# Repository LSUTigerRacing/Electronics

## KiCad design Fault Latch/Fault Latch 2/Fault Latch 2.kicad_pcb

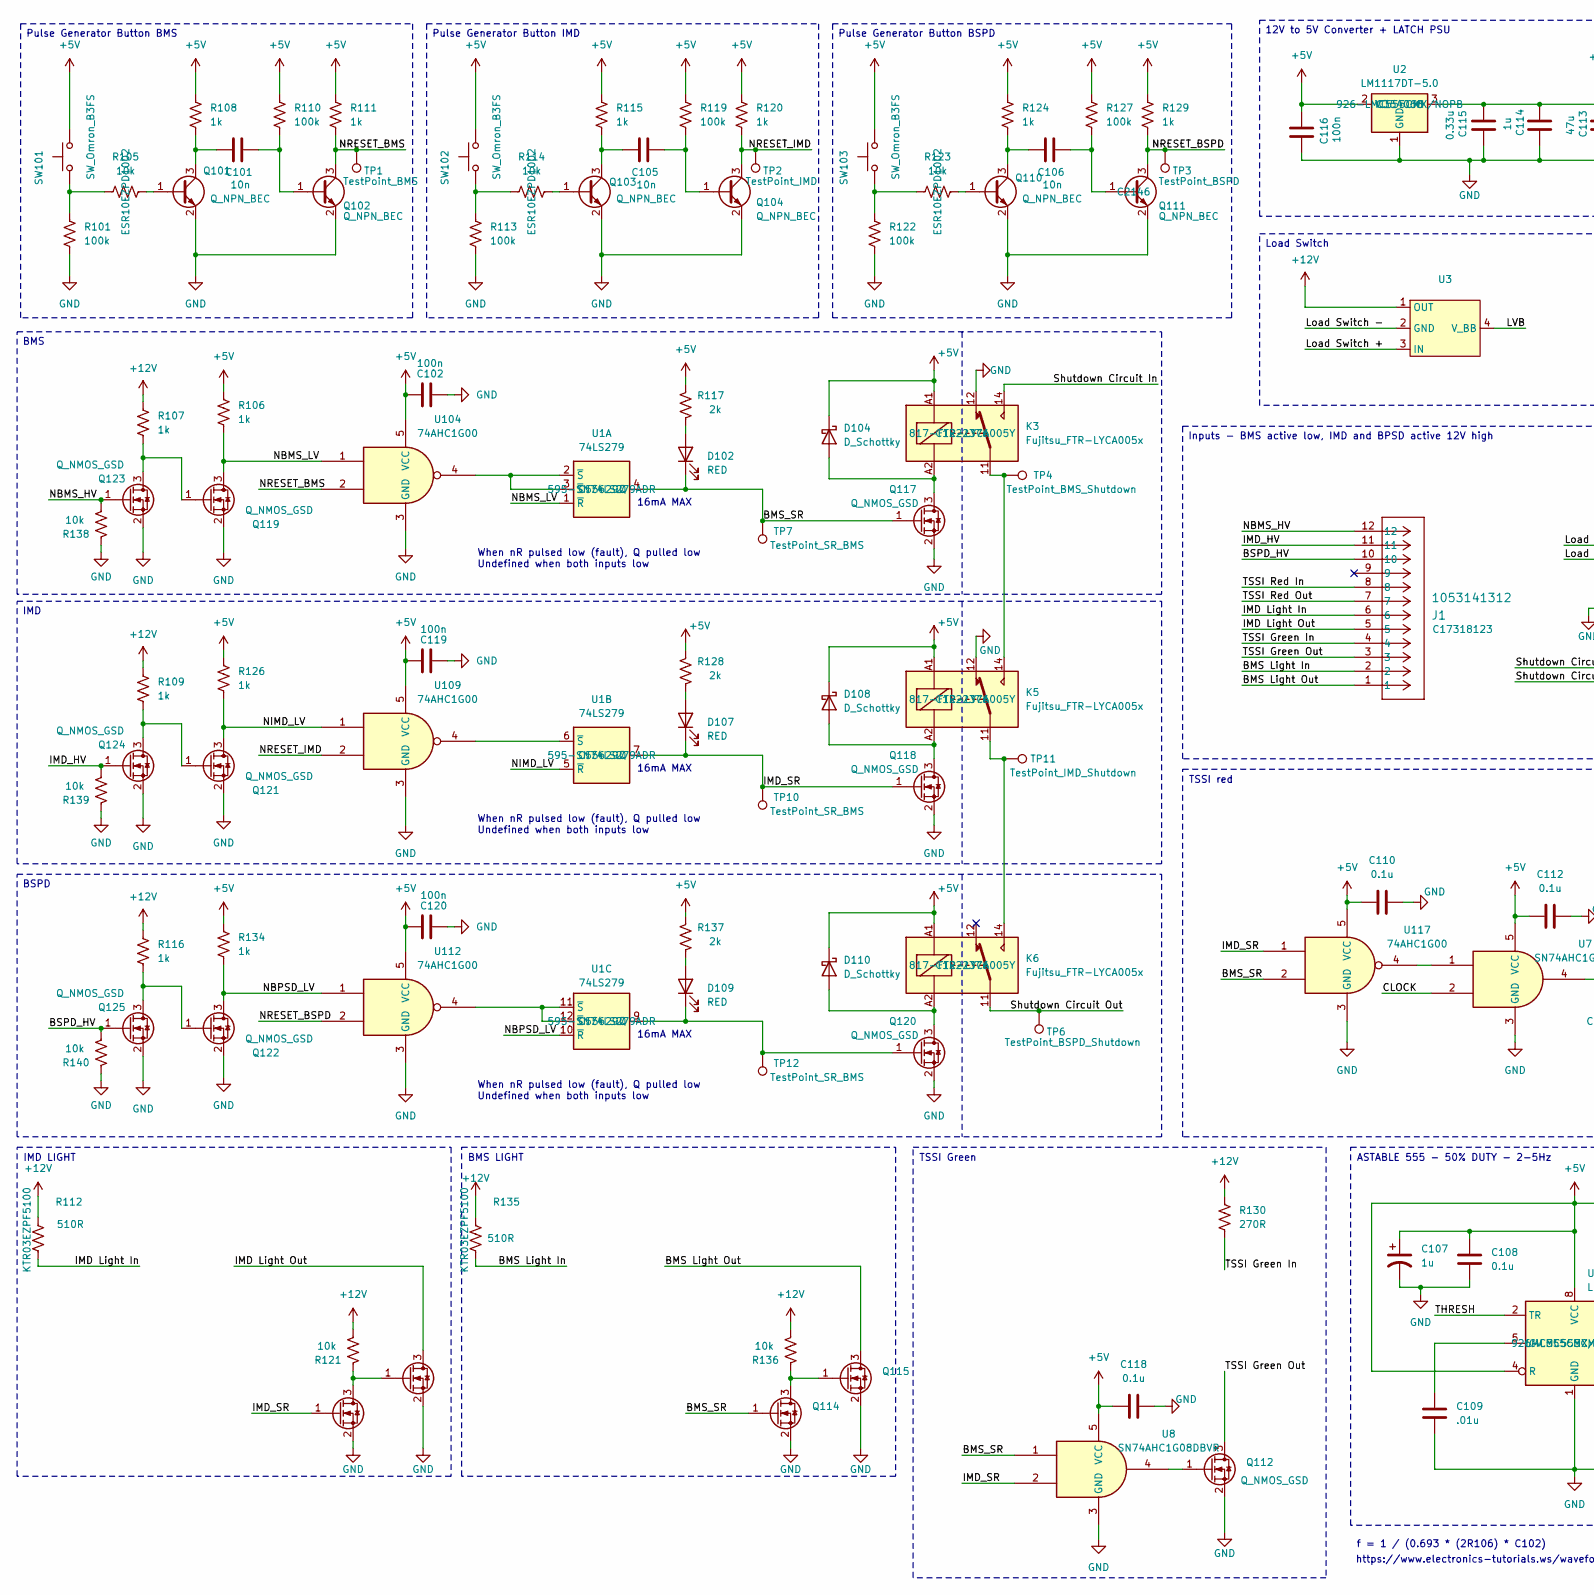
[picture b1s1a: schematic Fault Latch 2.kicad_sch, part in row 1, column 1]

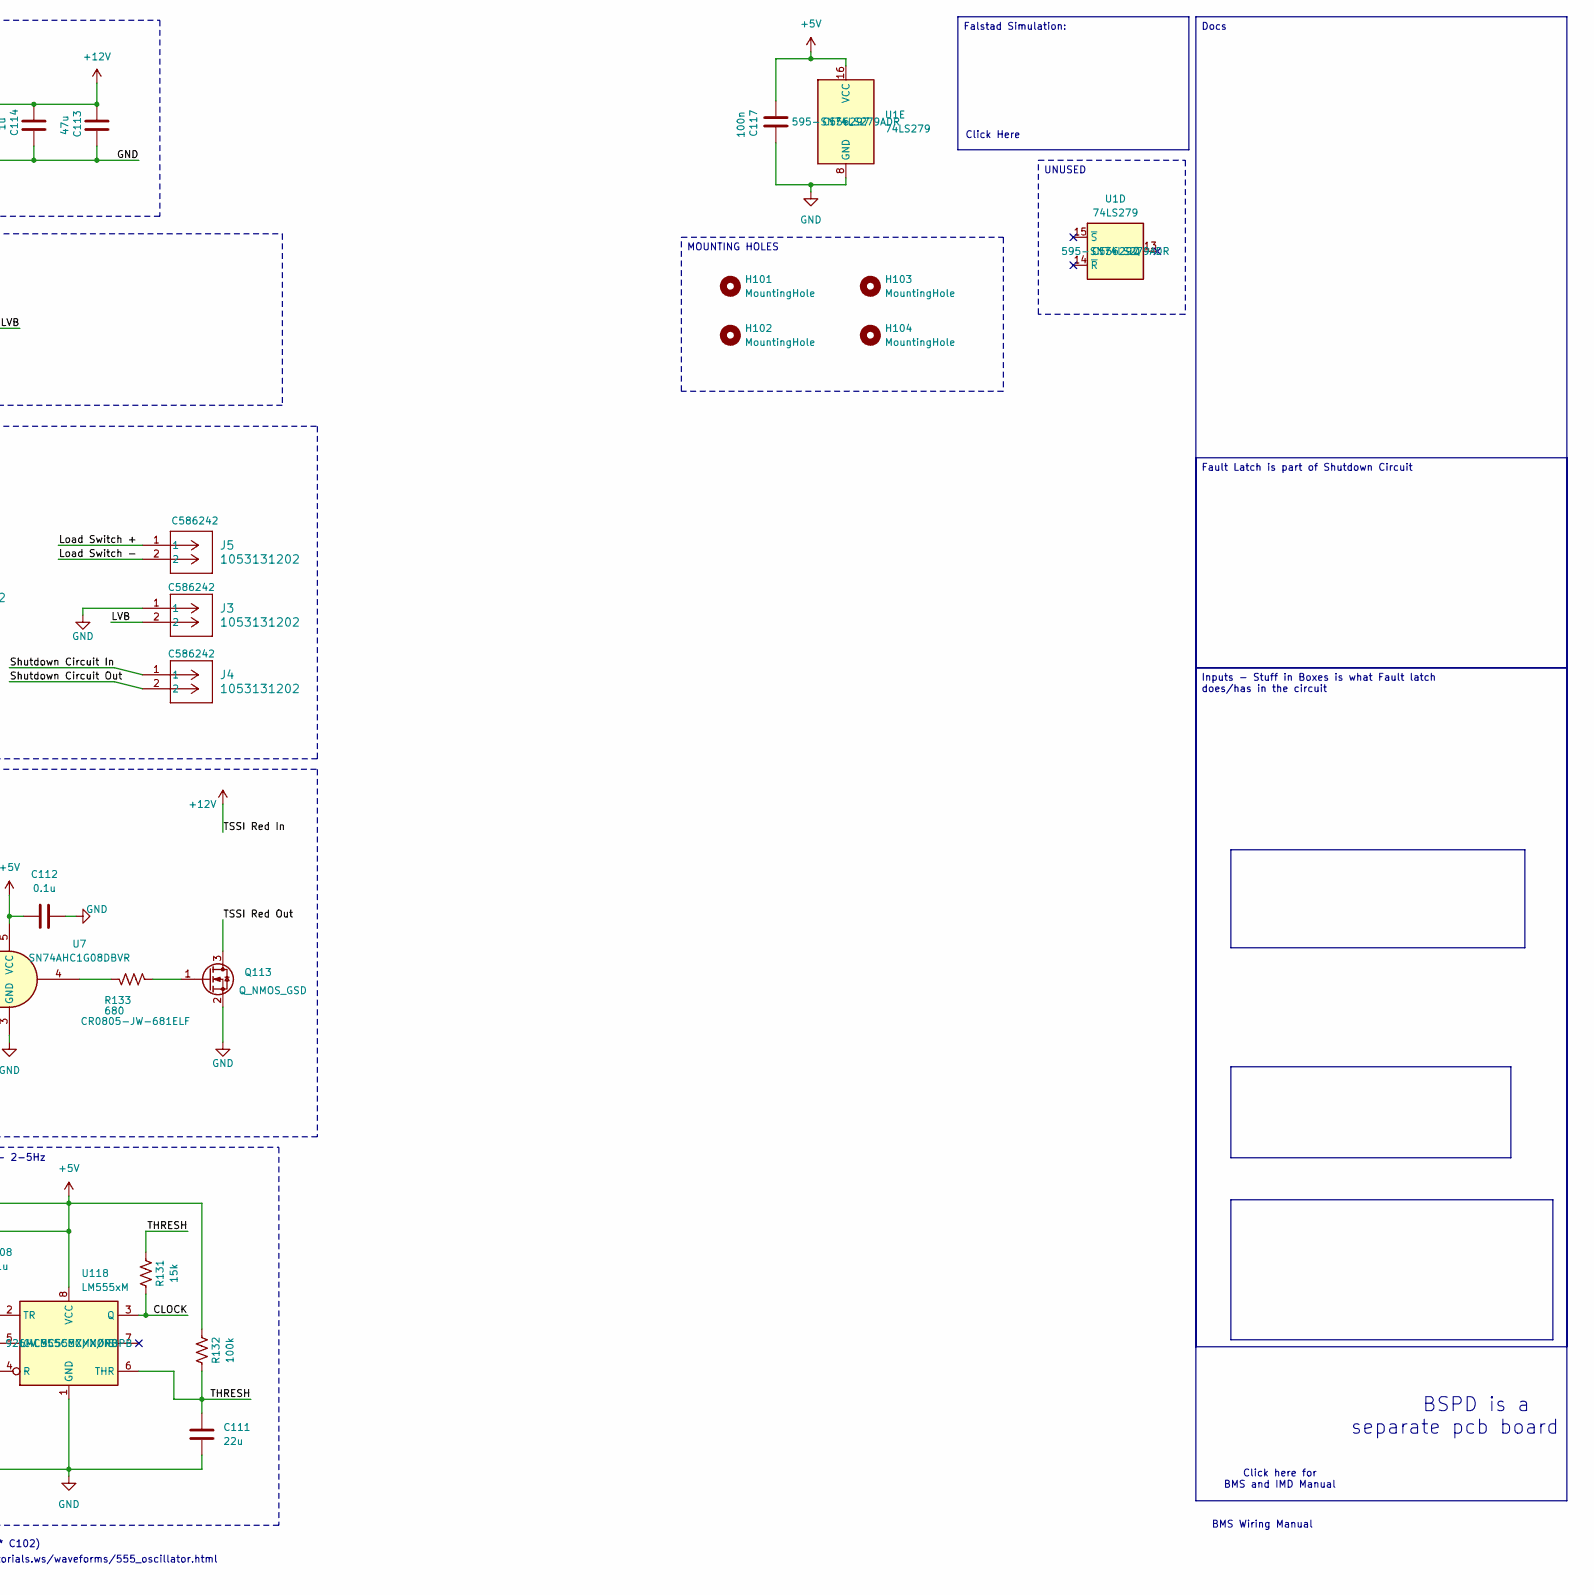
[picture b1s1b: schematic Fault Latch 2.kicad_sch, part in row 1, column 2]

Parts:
C101, C105, C106: 10n; C_0603_1608Metric_Pad1.08x0.95mm_HandSolder; JLC# C1589
C102, C116, C117, C119, C120: 100n; C_0603_1608Metric_Pad1.08x0.95mm_HandSolder; JLC# C1591
C107: 1u; C_0402_1005Metric; JLC# C59782
C108, C110, C112, C118: 0.1u; C_0402_1005Metric; JLC# C133086
C109: .01u; C_0402_1005Metric; JLC# C15195
C111: 22u; C_0402_1005Metric; JLC# C105226
C113: 47u; CP_Elec_6.3x5.4; JLC# C2836440
C114: 1u; C_0805_2012Metric_Pad1.18x1.45mm_HandSolder; JLC# C91186
C115: 0.33u; C_0603_1608Metric_Pad1.08x0.95mm_HandSolder; JLC# C282682
D102, D107, D109: RED; LED_0805_2012Metric_Pad1.15x1.40mm_HandSolder; JLC# C19171391
D104, D108, D110: D_Schottky; D_SMA; JLC# C8678
H101, H102, H103, H104: MountingHole; MountingHole_3.2mm_M3
J1: 1053141312; CONN_SD-105314-100_12_MOL; MOUSER 538-105314-1312
J3, J4, J5: 1053131202; Molex_Nano-Fit_105313-xx02_1x02_P2.50mm_Horizontal; MOUSER 538-105313-1202
K3, K5, K6: Fujitsu_FTR-LYCA005x; Relay_SPDT_Fujitsu_FTR-LYCA005x_FormC_Vertical; MOUSER 817-FTR-LYCA005Y
Q101, Q102, Q103, Q104, Q110, Q111: Q_NPN_BEC; SOT-23; JLC# C2146
Q105, Q106, Q112, Q113, Q114, Q115, Q117, Q118, Q119, Q120, Q121, Q122, Q123, Q124, Q125: Q_NMOS_GSD; SOT-23; JLC# C151421
R101, R110, R113, R119, R122, R127: 100k; R_0805_2012Metric_Pad1.20x1.40mm_HandSolder; JLC# C149504
R105, R114, R121, R123, R136, R138, R139, R140: 10k; R_0805_2012Metric_Pad1.20x1.40mm_HandSolder; JLC# C17414
R106, R107, R109, R116, R126, R134: 1k; R_0805_2012Metric_Pad1.20x1.40mm_HandSolder; JLC# C2889437
R108, R111, R115, R120, R124, R129: 1k; R_0805_2012Metric_Pad1.20x1.40mm_HandSolder; JLC# C17513
R112, R135: 510R; R_0603_1608Metric; JLC# KTR03EZPF5100
R117, R128, R137: 2k; R_0805_2012Metric_Pad1.20x1.40mm_HandSolder; JLC# C1359
R130: 270R; R_0603_1608Metric; JLC# C4151887
R131: 15k; R_0603_1608Metric; JLC# C22809
R132: 100k; R_0603_1608Metric; JLC# C60491
R133: 680; R_0805_2012Metric; Manufacturer_Part_Number CR0805-JW-681ELF; JLC# C1359
SW101, SW102, SW103: SW_Omron_B3FS; SW_SPST_Omron_B3FS-100xP; JLC# C271750
TP1: TestPoint_BMS; TestPoint_Pad_D1.5mm
TP2: TestPoint_IMD; TestPoint_Pad_D1.5mm
TP3: TestPoint_BSPD; TestPoint_Pad_D1.5mm
TP4: TestPoint_BMS_Shutdown; TestPoint_Pad_D1.5mm
TP6: TestPoint_BSPD_Shutdown; TestPoint_Pad_D1.5mm
TP7, TP10, TP12: TestPoint_SR_BMS; TestPoint_Pad_D1.5mm
TP11: TestPoint_IMD_Shutdown; TestPoint_Pad_D1.5mm
U1: 74LS279; SOIC-16_3.9x9.9mm_P1.27mm; MOUSER 595-SN74LS279ADR
U2: LM1117DT-5.0; TO-252-3_TabPin2; JLC# C354068
U3: SOT-223
U7, U8: SN74AHC1G08DBVR; SOT-23-5; JLC# C7467
U104, U109, U112, U117: 74AHC1G00; SOT-23-5; JLC# C350556
U118: LM555xM; SOIC-8_3.9x4.9mm_P1.27mm; Mouser Part Number 926-LMC555CMX/NOPB; JLC# C90760

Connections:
+5V: C102.1, C107.1, C108.1, C110.2, C112.2, C116.2, C117.1, C118.2, C119.1, C120.1, D104.1 (K), D108.1 (K), D110.1 (K), K3.A1, K5.A1, K6.A1, R106.1, R108.1, R110.1, R111.1, R115.1, R117.2, R119.1, R120.1, R124.1, R126.1, R127.1, R128.2, R129.1, R132.2, R134.1, R137.2, SW101.2, SW102.2, SW103.2, U1.16 (VCC), U2.2 (VO), U7.5 (VCC), U8.5 (VCC), U104.5 (VCC), U109.5 (VCC), U112.5 (VCC), U117.5 (VCC), U118.4 (R), U118.8 (VCC)
+12V: C113.1, C114.1, C115.1, J1.8, R107.1, R109.1, R112.1, R116.1, R121.1, R130.2, R135.1, R136.1, U2.3 (VI), U3.1 (OUT)
/BMS Light In: J1.2, R135.2
/BMS Light Out: J1.1, Q115.3 (D)
/BMS_SR: D102.1 (K), Q114.1 (G), Q117.1 (G), TP7.1, U1.4 (Q), U8.1, U117.2
/BSPD_HV: J1.10, Q125.1 (G), R140.1
/CLOCK: R131.1, U7.2, U118.3 (Q)
/IMD Light In: J1.6, R112.2
/IMD Light Out: J1.5, Q106.3 (D)
/IMD_HV: J1.11, Q124.1 (G), R139.1
/IMD_SR: D107.1 (K), Q105.1 (G), Q118.1 (G), TP10.1, U1.7 (Q), U8.2, U117.1
/LVB: J3.2, U3.4 (V_BB)
/Load Switch +: J5.1, U3.3 (IN)
/Load Switch -: J5.2, U3.2 (GND)
/NBMS_HV: J1.12, Q123.1 (G), R138.1
/NBMS_LV: Q119.3 (D), R106.2, U1.1 (~R), U104.1
/NBPSD_LV: Q122.3 (D), R134.2, U1.10 (~R), U112.1
/NIMD_LV: Q121.3 (D), R126.2, U1.5 (~R), U109.1
/NRESET_BMS: Q102.3 (C), R111.2, TP1.1, U104.2
/NRESET_BSPD: Q111.3 (C), R129.2, TP3.1, U112.2
/NRESET_IMD: Q104.3 (C), R120.2, TP2.1, U109.2
/Shutdown Circuit In: J4.1, K3.14
/Shutdown Circuit Out: J4.2, K6.11, TP6.1
/THRESH: C111.2, R131.2, R132.1, U118.2 (TR), U118.6 (THR)
/TSSI Green In: J1.4, R130.1
/TSSI Green Out: J1.3, Q112.3 (D)
/TSSI Red Out: J1.7, Q113.3 (D)
GND: C102.2, C107.2, C108.2, C109.2, C110.1, C111.1, C112.1, C113.2, C114.2, C115.2, C116.1, C117.2, C118.1, C119.2, C120.2, J3.1, K3.12, K5.12, Q101.2 (E), Q102.2 (E), Q103.2 (E), Q104.2 (E), Q105.2 (S), Q106.2 (S), Q110.2 (E), Q111.2 (E), Q112.2 (S), Q113.2 (S), Q114.2 (S), Q115.2 (S), Q117.2 (S), Q118.2 (S), Q119.2 (S), Q120.2 (S), Q121.2 (S), Q122.2 (S), Q123.2 (S), Q124.2 (S), Q125.2 (S), R101.2, R113.2, R122.2, R138.2, R139.2, R140.2, U1.8 (GND), U2.1 (GND), U7.3 (GND), U8.3 (GND), U104.3 (GND), U109.3 (GND), U112.3 (GND), U117.3 (GND), U118.1 (GND)
unnamed: D102.2 (A), R117.1
unnamed: D104.2 (A), K3.A2, Q117.3 (D)
unnamed: D107.2 (A), R128.1
unnamed: D108.2 (A), K5.A2, Q118.3 (D)
unnamed: D109.2 (A), R137.1
unnamed: D109.1 (K), Q120.1 (G), TP12.1, U1.9 (Q)
unnamed: D110.2 (A), K6.A2, Q120.3 (D)
unnamed: K3.11, K5.14, TP4.1
unnamed: K5.11, K6.14, TP11.1
unnamed: Q101.1 (B), R105.1
unnamed: C101.1, Q101.3 (C), R108.2
unnamed: C101.2, Q102.1 (B), R110.2
unnamed: Q103.1 (B), R114.1
unnamed: C105.1, Q103.3 (C), R115.2
unnamed: C105.2, Q104.1 (B), R119.2
unnamed: Q105.3 (D), Q106.1 (G), R121.2
unnamed: Q110.1 (B), R123.1
unnamed: C106.1, Q110.3 (C), R124.2
unnamed: C106.2, Q111.1 (B), R127.2
unnamed: Q112.1 (G), U8.4
unnamed: Q113.1 (G), R133.1
unnamed: Q114.3 (D), Q115.1 (G), R136.2
unnamed: Q119.1 (G), Q123.3 (D), R107.2
unnamed: Q121.1 (G), Q124.3 (D), R109.2
unnamed: Q122.1 (G), Q125.3 (D), R116.2
unnamed: R101.1, R105.2, SW101.1
unnamed: R113.1, R114.2, SW102.1
unnamed: R122.1, R123.2, SW103.1
unnamed: R133.2, U7.4
unnamed: U1.6 (~S), U109.4
unnamed: U1.2 (~S), U1.3 (~S), U104.4
unnamed: U1.11 (~S), U1.12 (~S), U112.4
unnamed: U7.1, U117.4
unnamed: C109.1, U118.5 (CV)

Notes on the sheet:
16mA MAX
BMS Wiring Manual
When nR pulsed low (fault), Q pulled low Undefined when both inputs low
Click here for BMS and IMD Manual
BSPD is a separate pcb board
f = 1 / (0.693 * (2R106) * C102)
https://www.electronics-tutorials.ws/waveforms/555_oscillator.html
Click Here
UNUSED
Pulse Generator Button BMS
Inputs - Stuff in Boxes is what Fault latch does/has in the circuit
TSSI red
BSPD
BMS
Load Switch
Pulse Generator Button BSPD
TSSI Green
ASTABLE 555 - 50% DUTY - 2-5Hz
Fault Latch is part of Shutdown Circuit
Docs
Pulse Generator Button IMD
12V to 5V Converter + LATCH PSU
MOUNTING HOLES
Inputs - BMS active low, IMD and BPSD active 12V high
BMS LIGHT
IMD
Falstad Simulation:
IMD LIGHT

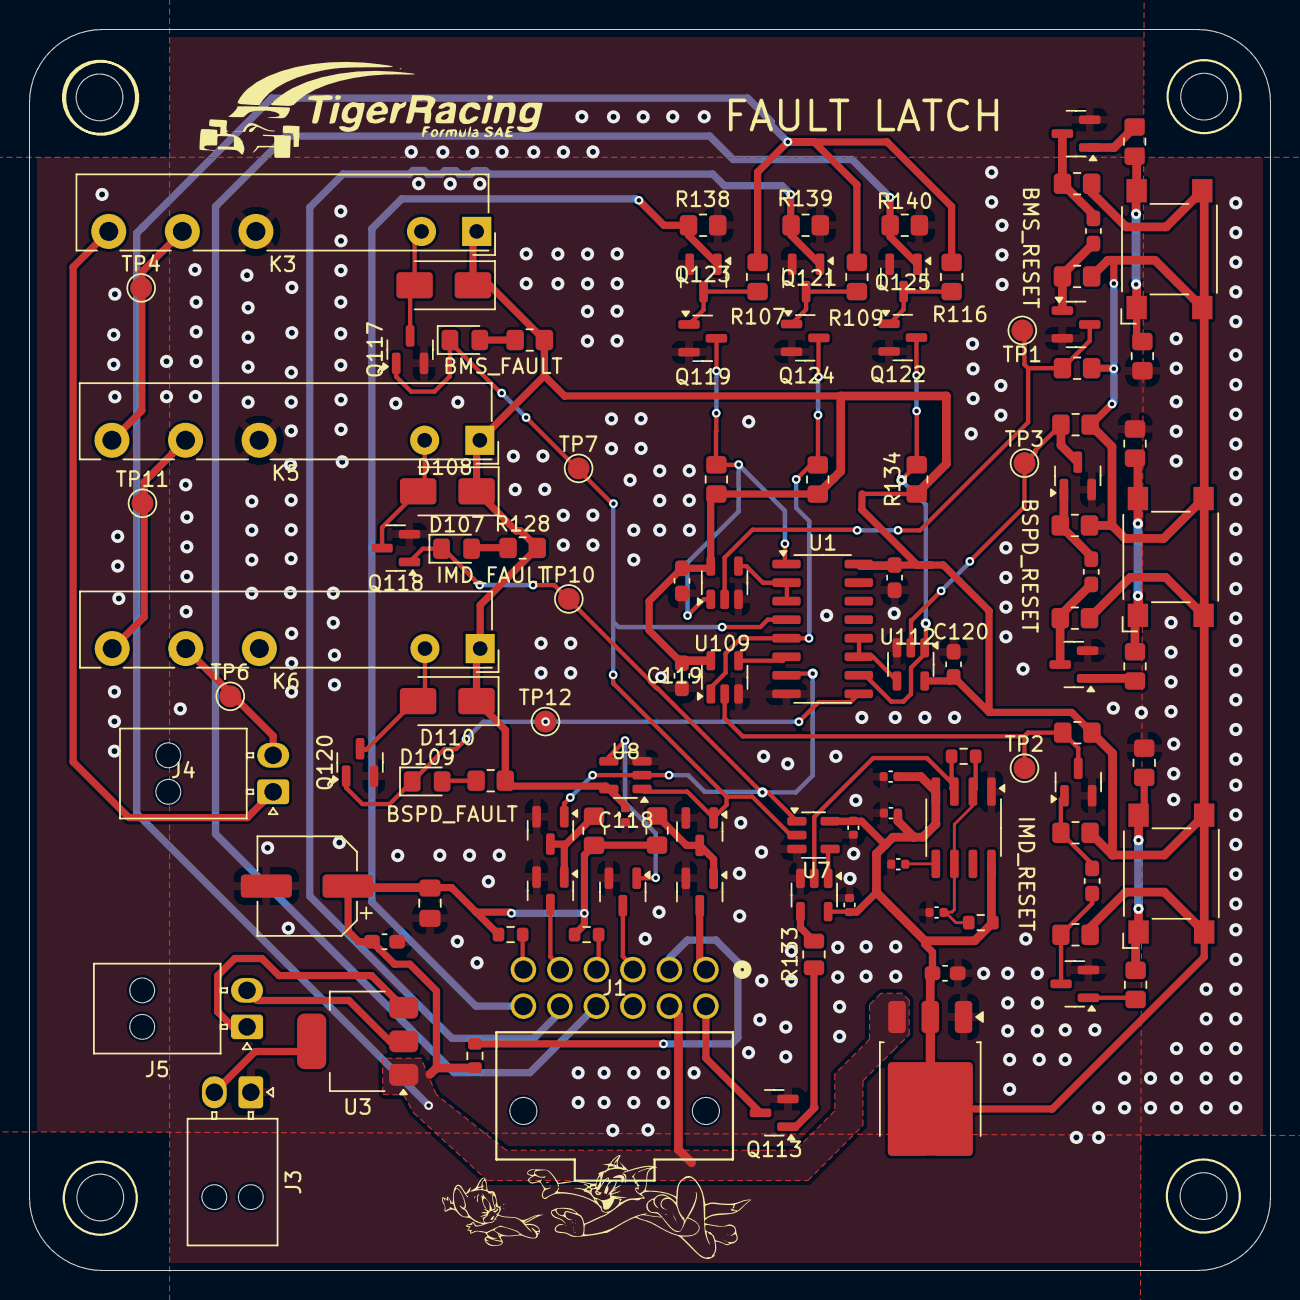
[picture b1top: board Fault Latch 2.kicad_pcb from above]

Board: 2 copper layers, 85.0 x 85.0 mm, 113 parts (0 on the bottom side), 62 nets.

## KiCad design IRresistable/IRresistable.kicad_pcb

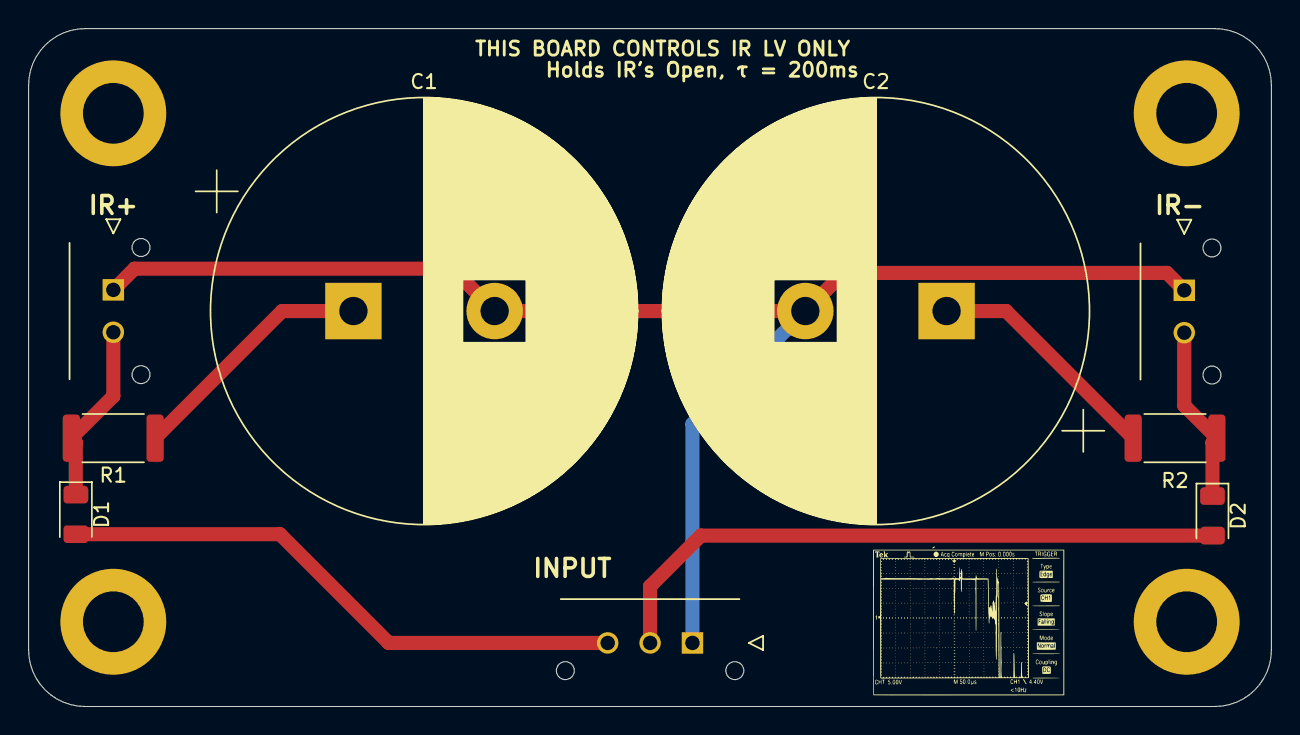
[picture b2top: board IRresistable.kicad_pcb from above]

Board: 2 copper layers, 88.0 x 48.0 mm, 13 parts (0 on the bottom side), 7 nets.

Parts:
C1, C2: 4.7m; CP_Radial_D30.0mm_P10.00mm_SnapIn
D1, D2: SD1206T020S1R0; D_1206_3216Metric
H1, H2, H3, H4: MountingHole; MountingHole_4.3mm_M4_DIN965_Pad
INPUT: MicroFit 3-Pos
IR+: MicroFit 2-Pos
IR-: MicroFit 2-Pos
R1, R2: 10; R_2512_6332Metric

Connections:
/IR+ HOLD: D1.1 (K), IR+.2, R1.2
/IR+ INPUT: D1.2 (A), INPUT.3
/IR- HOLD: D2.1 (K), IR-.2, R2.2
/IR- INPUT: D2.2 (A), INPUT.2
GNDPWR: C1.2, C2.2, INPUT.1, IR+.1, IR-.1
unnamed: C1.1, R1.1
unnamed: C2.1, R2.1

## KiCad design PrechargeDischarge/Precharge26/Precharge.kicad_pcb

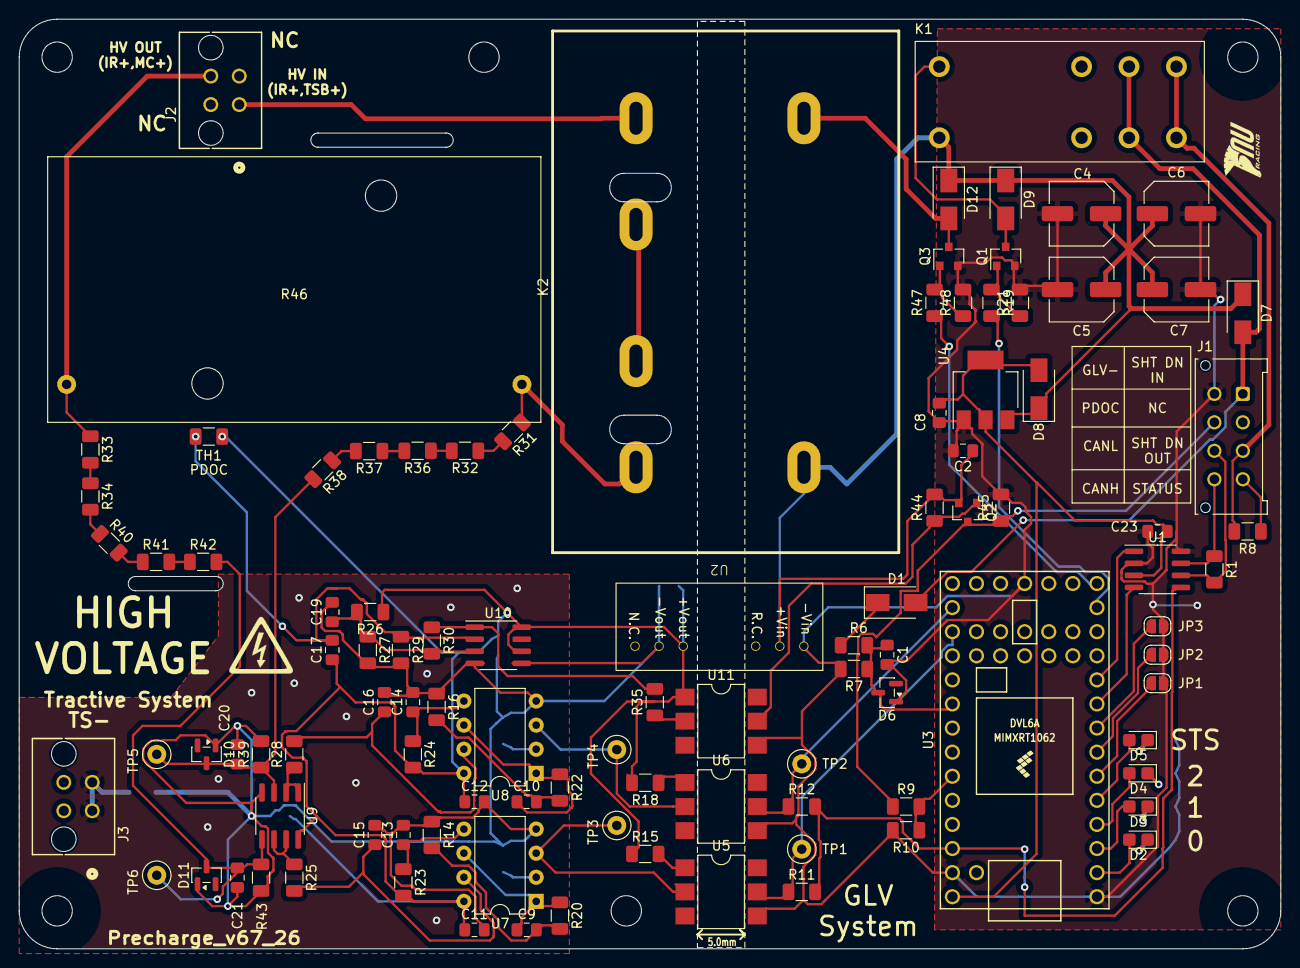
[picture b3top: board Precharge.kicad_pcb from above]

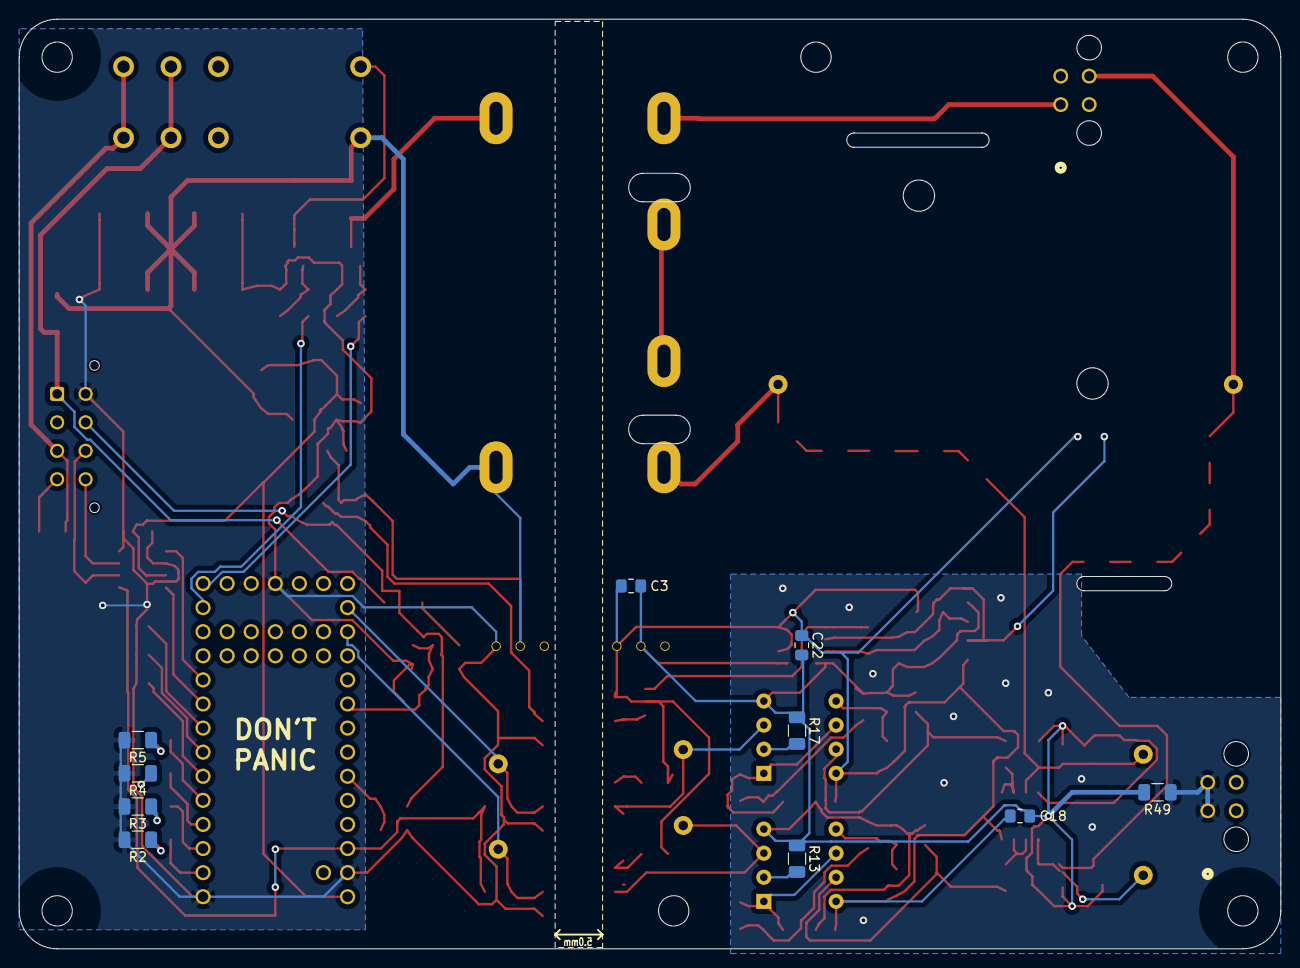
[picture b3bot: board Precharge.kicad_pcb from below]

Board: 2 copper layers, 133.0 x 98.0 mm, 119 parts (10 on the bottom side), 68 nets.

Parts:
C1, C2, C11, C12, C15, C16, C17, C18, C19, C20, C21, C22, C23: 100n; C_0805_2012Metric_Pad1.15x1.40mm_HandSolder
C3, C8, C9, C10: 1u; C_0805_2012Metric_Pad1.15x1.40mm_HandSolder
C4, C5, C6, C7: 220u; C_Elec_6.3x5.4
C13, C14: 10n; C_0805_2012Metric_Pad1.15x1.40mm_HandSolder
D1, D7, D8, D9, D12: D; D_SMA
D2, D3, D4, D5: LED; LED_0805_2012Metric_Castellated
D6: BZX84C3V3; SOT-23
D10, D11: BZX84C12; SOT-23
J1: MicroFit; Molex_Micro-Fit_3.0_43045-0812_2x04_P3.00mm_Vertical
J2: Mini-Fit_Jr_5566-04A; MICROFIT-4PIN
J3: 447690401; MICROFIT-4PIN
JP1, JP2, JP3: SolderJumper_2_Open; SolderJumper-2_P1.3mm_Open_RoundedPad1.0x1.5mm
K1: OMRON-G2RL-24; OMRON-G2R-24
K2: G7L-2A-X-L
MT1, MT2, MT3, MT4, MT5, MT6: MountingHole_3.2mm_M3
Q1, Q3: 2N7002; SOT-23
Q2: MMBT3906; SOT-23
R1: 160; R_1206_3216Metric
R2, R3, R4, R5: 200; R_1206_3216Metric
R6, R9: 20k; R_1206_3216Metric
R7, R10, R23, R24: 6k8; R_1206_3216Metric
R8, R21, R27, R29, R44, R45, R48: 10k; R_1206_3216Metric
R11, R12: 1k5; R_1206_3216Metric
R13, R17, R26: 12k; R_1206_3216Metric
R14, R16: 47; R_1206_3216Metric
R15, R18: 560; R_1206_3216Metric
R19, R47: 220; R_1206_3216Metric
R20, R22, R25, R28: 100k; R_1206_3216Metric
R30: 500k; R_1206_3216Metric
R31, R32, R33, R34, R36, R37, R38, R40, R41, R42: 510k; R_1206_3216Metric
R35: 2k2; R_1206_3216Metric
R39, R43: 39k; R_1206_3216Metric
R46: HSA253K3J; Chassis_Resistor_TE_Connectivity_HSA25
R49: 0; R_1206_3216Metric
TH1: TFPT1206L1002FM; R_1206_3216Metric
TP1, TP2, TP3, TP4, TP5, TP6: TestPoint; TestPoint_Loop_D2.50mm_Drill1.0mm_LowProfile
U1: TJA1051T-3; SOIC-8_3.9x4.9mm_P1.27mm
U2: SPAN02A-12; DC-DCSPAN02W8-12
U3: Teensy4.0; Teensy40
U4: LM1117-5.0; SOT-223-3_TabPin2
U5, U6, U11: 4N35; SMDIP-6_W7.62mm
U7, U8: LM331; DIP-8_W7.62mm
U9: LM2904; SOIC-8_3.9x4.9mm_P1.27mm
U10: LM393; SOIC-8_3.9x4.9mm_P1.27mm

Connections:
+3V3: R11.2, R12.2, U1.5 (VIO), U3.31
+5V: C8.1, C23.2, D8.2 (A), U1.3 (VCC), U3.33, U4.2 (VO)
+12P: C3.2, C11.1, C12.1, C17.1, C18.1, C22.1, R15.1, R18.2, R23.2, R24.2, R26.1, TH1.2, U2.6 (+Vout), U7.8 (VS), U8.8 (VS), U9.8 (V+), U10.6 (-), U10.8 (V+), U11.1
+12V: C2.1, C4.1, C5.1, C6.1, C7.1, D7.1 (K), D8.1 (K), D9.1 (K), D12.1 (K), K1.8, K2.0, Q2.2 (E), R44.2, U2.2 (+Vin), U4.3 (VI)
/CANH: J1.8, R1.1, U1.7 (CANH)
/CANL: J1.7, R1.2, U1.6 (CANL)
/CANRX: U1.4 (RXD), U3.9
/CANTX: U1.1 (TXD), U3.10
/CFG0: JP1.1 (A), U3.6
/CFG1: JP2.1 (A), U3.7
/CFG2: JP3.1 (A), U3.8
/Faccu: R12.1, TP2.1, U3.21, U6.5
/FoutAccu: TP4.1, U6.2, U8.3 (FOUT)
/FoutTS: TP3.1, U5.2, U7.3 (FOUT)
/Fts: R11.1, TP1.1, U3.22, U5.5
/PDOC_OK: J1.6, Q2.3 (C), R9.1, R45.1
/PRECHG: R47.1, U3.14
/PRECH_STS: J1.4, R8.1
/PWR_OK: C1.1, D6.3 (K), R6.2, R7.1, U3.25
/SHTDN_CTRL: R19.2, U3.13
/SHTDN_OUT: J1.3, K1.4, K1.5, R8.2
/TS-: J3.1, J3.2, R49.1
/VinAccu: K2.2, R31.1, R46.1
/VinTS: J2.4, R33.1, R46.2
GLV+: D1.2 (A), D7.2 (A), J1.1, K1.3, K1.6
GLV-: C1.2, C2.2, C4.2, C5.2, C6.2, C7.2, C8.2, C23.1, D6.1 (A), J1.5, JP1.2 (B), JP2.2 (B), JP3.2 (B), Q1.2 (S), Q3.2 (S), R2.2, R3.2, R4.2, R5.2, R7.2, R10.2, R21.2, R45.2, R48.2, U1.2 (GND), U1.8 (S), U2.1 (-Vin), U3.1, U3.17, U3.32, U4.1 (GND), U5.4, U6.4, U11.4
GNDS: C3.1, C11.2, C12.2, C13.2, C14.2, C15.2, C16.2, C18.2, C19.2, C20.2, C21.2, C22.2, D10.1 (A), D11.1 (A), R13.1, R14.1, R16.1, R17.1, R27.2, R29.2, R39.2, R43.2, R49.2, U2.7 (-Vout), U7.4 (GND), U8.4 (GND), U9.4 (V-), U10.4 (V-), U10.5 (+)
unnamed: C9.2, R14.2, R20.2
unnamed: C10.2, R16.2, R22.2
unnamed: D1.1 (K), R6.1
unnamed: D2.1 (K), R2.1
unnamed: D3.1 (K), R3.1
unnamed: D4.1 (K), R4.1
unnamed: D5.1 (K), R5.1
unnamed: D9.2 (A), K1.1, Q1.3 (D)
unnamed: C20.1, D10.3 (K), R38.2, R39.1, TP5.1, U9.3 (+)
unnamed: C21.1, D11.3 (K), R42.2, R43.1, TP6.1, U9.5 (+)
unnamed: D12.2 (A), K2.1, Q3.3 (D)
unnamed: J2.1, K2.8
unnamed: K2.4, K2.6
unnamed: Q1.1 (G), R19.1, R21.1
unnamed: Q2.1 (B), R44.1, U11.5
unnamed: Q3.1 (G), R47.2, R48.1
unnamed: R9.2, R10.1, U3.28
unnamed: R15.2, U5.1
unnamed: R18.1, U6.1
unnamed: R30.1, R35.2, U10.1
unnamed: R31.2, R32.1
unnamed: R32.2, R36.1
unnamed: R33.2, R34.1
unnamed: R34.2, R40.1
unnamed: R35.1, U11.2
unnamed: R36.2, R37.1
unnamed: R37.2, R38.1
unnamed: R40.2, R41.1
unnamed: R41.2, R42.1
unnamed: C15.1, R25.2, U7.7 (CIN)
unnamed: C9.1, R20.1, U7.1 (IOUT), U7.6 (THR)
unnamed: R13.2, U7.2 (IREF)
unnamed: C13.1, R23.1, U7.5 (RC)
unnamed: C16.1, R28.2, U8.7 (CIN)
unnamed: C10.1, R22.1, U8.1 (IOUT), U8.6 (THR)
unnamed: R17.2, U8.2 (IREF)
unnamed: C14.1, R24.1, U8.5 (RC)
unnamed: R28.1, U9.1, U9.2 (-)
unnamed: R25.1, U9.6 (-), U9.7
unnamed: C19.1, R26.2, R27.1, R30.2, U10.3 (+)
unnamed: C17.2, R29.1, TH1.1, U10.2 (-)

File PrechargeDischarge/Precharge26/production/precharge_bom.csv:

Designator,Footprint,Quantity,Value,LCSC Part #
"C1, C11, C12, C15, C16, C17, C18, C19, C2, C20, C21, C22, C23",0805,13,100n,
"C10, C3, C8, C9",0805,4,1u,
"C13, C14",0805,2,10n,
"C4, C5, C6, C7",C_Elec_6.3x5.4,4,220u,
"D1, D12, D7, D8, D9",D_SMA,5,D,
"D10, D11",SOT-23,2,BZX84C12,
"D2, D3, D4, D5",0805,4,LED,
D6,SOT-23,1,BZX84C3V3,
J1,Molex_Micro-Fit_3.0_43045-0812_2x04_P3.00mm_Vertical,1,MicroFit,
J2,MICROFIT-4PIN,1,Mini-Fit_Jr_5566-04A,
J3,MICROFIT-4PIN,1,447690401,
"JP1, JP2, JP3",SolderJumper-2_P1.3mm_Open_RoundedPad1.0x1.5mm,3,SolderJumper_2_Open,
K1,OMRON-G2R-24,1,OMRON-G2RL-24,C1524522
K2,G7L-2A-X-L,1,G7L-2A-X-L,
"Q1, Q3",SOT-23,2,2N7002,
Q2,SOT-23,1,MMBT3906,
R1,1206,1,160,
"R10, R23, R24, R7",1206,4,6k8,
"R11, R12",1206,2,1k5,
"R13, R17, R26",1206,3,12k,
"R14, R16",1206,2,47,
"R15, R18",1206,2,560,
"R19, R47",1206,2,220,
"R2, R3, R4, R5",1206,4,200,
"R20, R22, R25, R28",1206,4,100k,
"R21, R27, R29, R44, R45, R48, R8",1206,7,10k,
R30,1206,1,500k,
"R31, R32, R33, R34, R36, R37, R38, R40, R41, R42",1206,10,510k,
R35,1206,1,2k2,
"R39, R43",1206,2,39k,
R46,Chassis_Resistor_TE_Connectivity_HSA25,1,HSA253K3J,
R49,1206,1,0,
"R6, R9",1206,2,20k,
TH1,1206,1,TFPT1206L1002FM,
"TP1, TP2, TP3, TP4, TP5, TP6",TestPoint_Loop_D2.50mm_Drill1.0mm_LowProfile,6,TestPoint,
U1,SOIC-8_3.9x4.9mm_P1.27mm,1,TJA1051T-3,
U10,SOIC-8_3.9x4.9mm_P1.27mm,1,LM393,
"U11, U5, U6",SMDIP-6_W7.62mm,3,4N35,
U2,DC-DCSPAN02W8-12,1,SPAN02A-12,
U3,Teensy40,1,Teensy4.0,
U4,SOT-223-3_TabPin2,1,LM1117-5.0,
"U7, U8",DIP-8_W7.62mm,2,LM331,
U9,SOIC-8_3.9x4.9mm_P1.27mm,1,LM2904,

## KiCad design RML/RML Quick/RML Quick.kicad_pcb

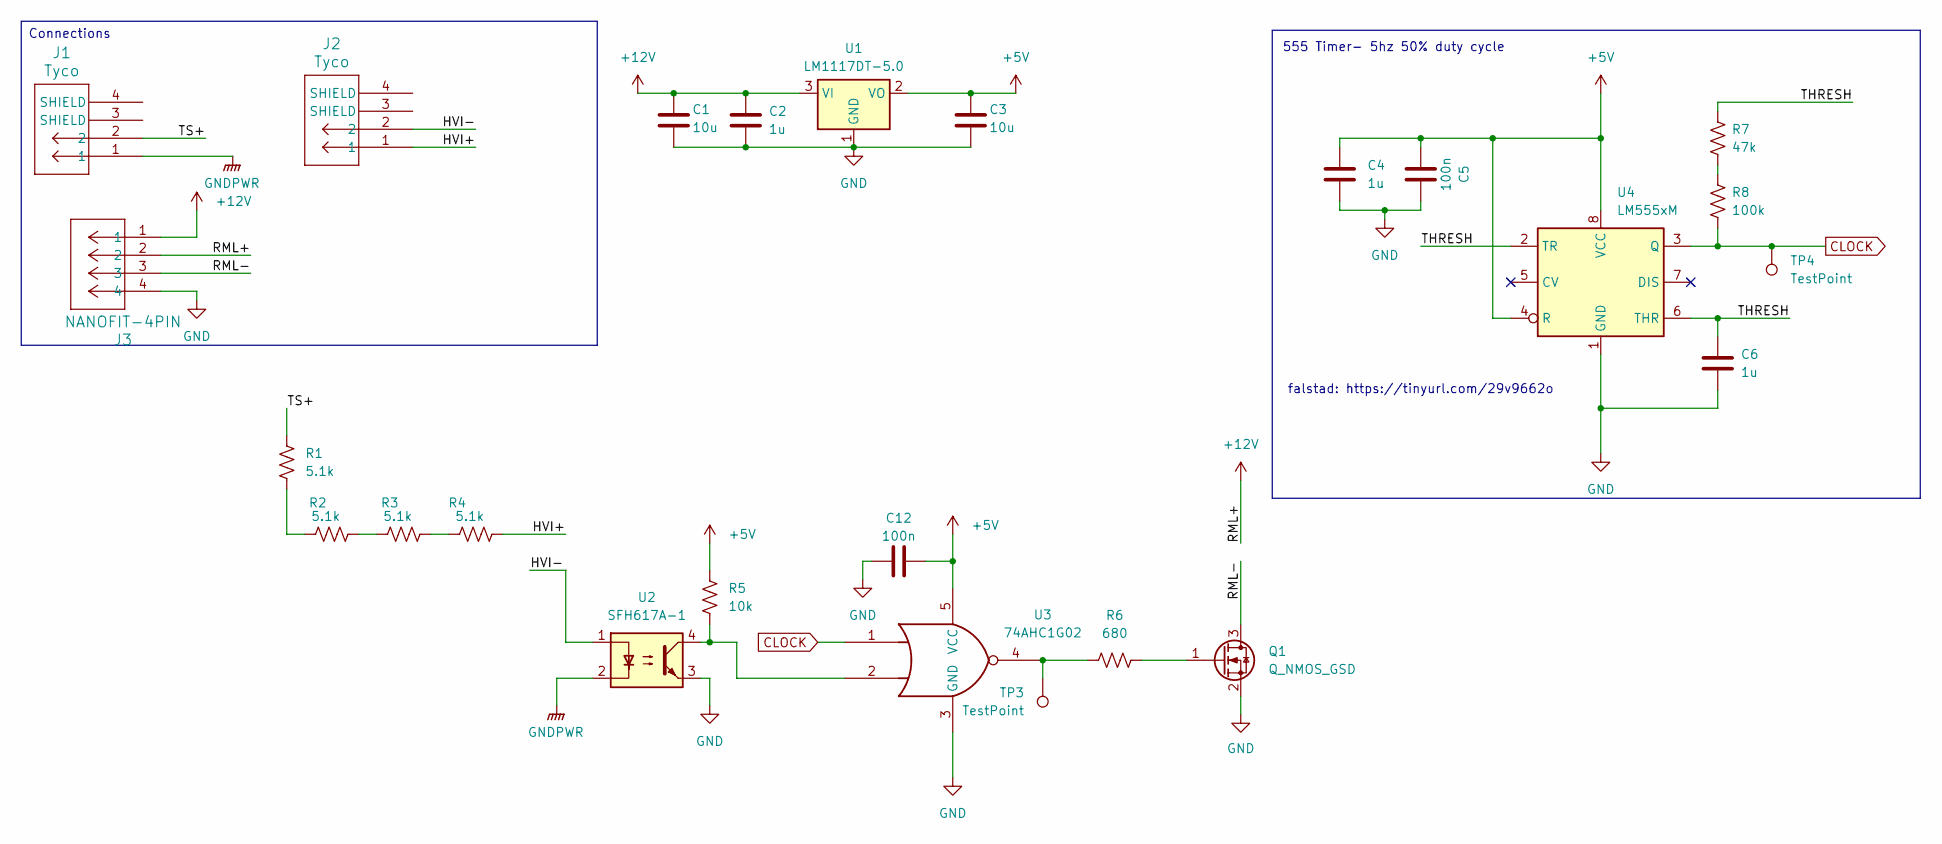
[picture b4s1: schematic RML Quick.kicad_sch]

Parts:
C1, C3: 10u; C_0603_1608Metric; JLC# C70225
C2, C4, C6: 1u; C_0603_1608Metric; JLC# C1592
C5, C12: 100n; C_0603_1608Metric; JLC# C1590
J1, J2: Tyco; tyco
J3: NANOFIT-4PIN; SAMMY-4PIN
Q1: Q_NMOS_GSD; SOT-23; JLC# C2590
R1, R2, R3, R4: 5.1k; R_Axial_DIN0516_L15.5mm_D5.0mm_P7.62mm_Vertical; MFR# RR03J5K1TB
R5: 10k; R_1206_3216Metric; JLC# C1489
R6: 680; R_0805_2012Metric; MFR# CR0805-JW-681ELF
R7: 47k; R_1206_3216Metric; JLC# C25664
R8: 100k; R_1206_3216Metric; JLC# C17900
TP3, TP4: TestPoint; TestPoint_Pad_1.0x1.0mm
U1: LM1117DT-5.0; TO-252-3_TabPin2; JLC# C354068
U2: SFH617A-1; DIP-4_W7.62mm; MOUSER SFH617A-1
U3: 74AHC1G02; SOT-23-5; Mouser 595-SN74AHC1G02DBE4
U4: LM555xM; SOIC-8_3.9x4.9mm_P1.27mm; JLC# C90760

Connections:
+5V: C3.1, C4.1, C5.1, C12.2, R5.1, U1.2 (VO), U3.5 (VCC), U4.4 (R), U4.8 (VCC)
+12V: C1.1, C2.1, J3.1, J3.2, U1.3 (VI)
/HVI+: J2.1, R4.2
/HVI-: J2.2, U2.1
/RML-: J3.3, Q1.3 (D)
/THRESH: C6.1, R7.1, U4.2 (TR), U4.6 (THR)
/TS+: J1.2, R1.1
CLOCK: R8.2, TP4.1, U3.1, U4.3 (Q)
GND: C1.2, C2.2, C3.2, C4.2, C5.2, C6.2, C12.1, J3.4, Q1.2 (S), U1.1 (GND), U2.3, U3.3 (GND), U4.1 (GND)
GNDPWR: J1.1, U2.2
unnamed: Q1.1 (G), R6.2
unnamed: R1.2, R2.1
unnamed: R2.2, R3.1
unnamed: R3.2, R4.1
unnamed: R5.2, U2.4, U3.2
unnamed: R6.1, TP3.1, U3.4
unnamed: R7.2, R8.1

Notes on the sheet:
555 Timer- 5hz 50% duty cycle
falstad: https://tinyurl.com/29v9662o
Connections

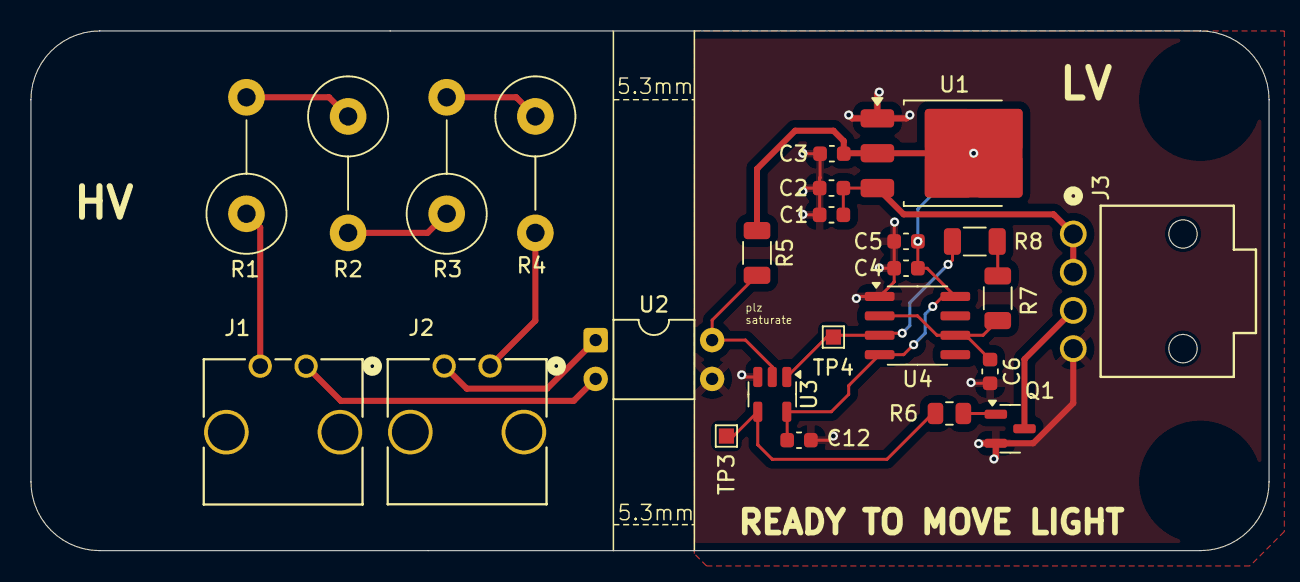
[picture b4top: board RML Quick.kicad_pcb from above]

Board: 2 copper layers, 81.0 x 34.0 mm, 25 parts (0 on the bottom side), 17 nets.
